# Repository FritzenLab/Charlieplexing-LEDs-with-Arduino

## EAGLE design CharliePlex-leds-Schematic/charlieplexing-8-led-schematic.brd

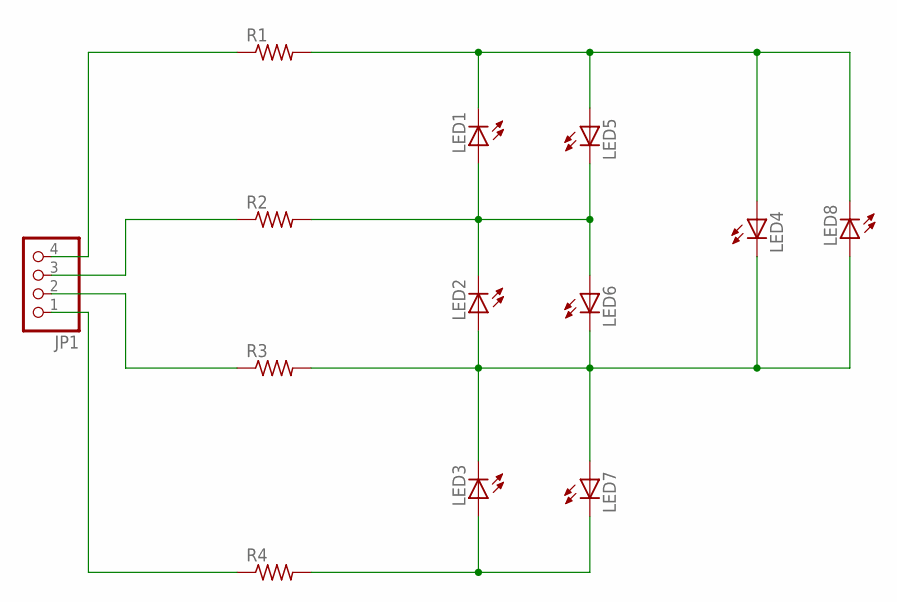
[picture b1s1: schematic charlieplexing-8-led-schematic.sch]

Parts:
JP1: PINHD-1X4; 1X04
LED1, LED2, LED3, LED4: LED5MM
LED5, LED6, LED7, LED8: LED3MM
R1, R2, R3, R4: R-US_0207/10; 0207/10

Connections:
unnamed: LED1.A, LED2.K (C), LED5.K (C), LED6.A, R2.2
unnamed: LED2.A, LED3.K (C), LED4.K (C), LED6.K (C), LED7.A, LED8.A, R3.2
unnamed: LED3.A, LED7.K (C), R4.2
unnamed: JP1.4, R1.1
unnamed: JP1.3, R2.1
unnamed: JP1.2, R3.1
unnamed: JP1.1, R4.1
unnamed: LED1.K (C), LED4.A, LED5.A, LED8.K (C), R1.2

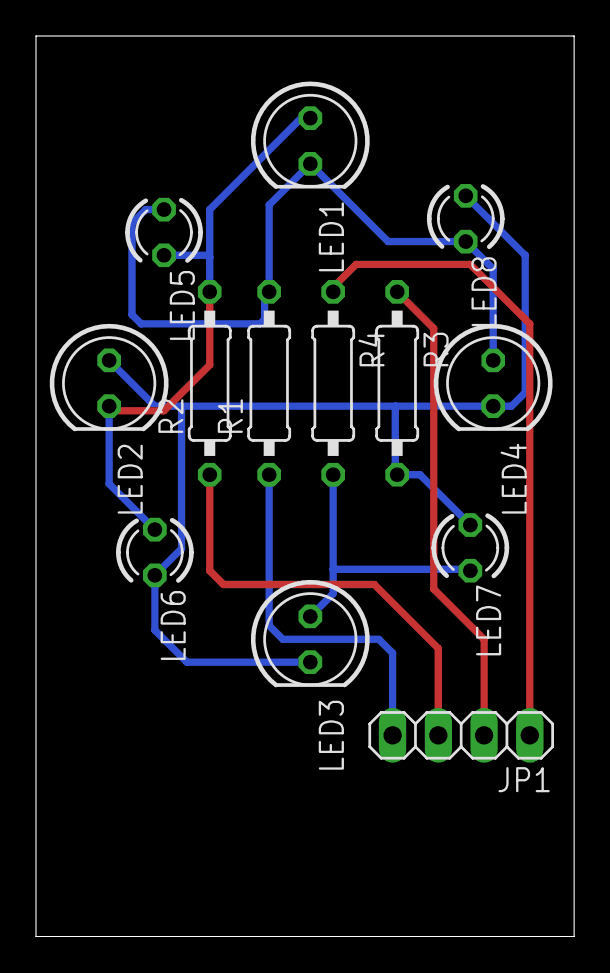
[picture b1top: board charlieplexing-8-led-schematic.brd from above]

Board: 2 copper layers, 29.9 x 50.0 mm, 13 parts (0 on the bottom side), 8 nets.

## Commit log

2018-04-07 added schematic and code
    added schematic and code
2018-04-07 added images and video
    added images and video of the charlieplexing hardware+software working
2018-04-07 changd time to 62mS
    changd time to 62mS
2018-04-07 added GIF image of the chalieplexing
    added GIF image of the chalieplexing
2018-04-07 added schematic diagram image
    added schematic diagram image
2019-03-05 criada PCI display LED 7 segmentos
    criada PCI display LED 7 segmentos
